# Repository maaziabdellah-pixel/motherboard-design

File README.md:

# Smart Earbuds Charging PCB

A PCB designed to manage charging, battery protection and power delivery for wireless earbuds.
changes:
- Added a new section on the design considerations for the PCB.

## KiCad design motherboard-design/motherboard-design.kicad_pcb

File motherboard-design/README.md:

# Smart Earbuds Charging PCB

A compact 2‑layer PCB that manages charging, protection and power delivery for
the rechargeable battery inside a wireless‑earbuds charging case. It takes 5 V
from a USB Type‑C input, charges a single‑cell 3.7 V Li‑ion battery with a
TP4056, protects the cell with a DW01A + dual‑MOSFET circuit, and shows charge
status on two LEDs.

Designed in **KiCad 10**. Schematic (ERC) and layout (DRC) are both **clean –
0 errors, 0 warnings, 0 unconnected nets.**

---

## 1. Project purpose

| Requirement | How it is met |
|---|---|
| Charge a single‑cell 3.7 V Li‑ion battery | TP4056 linear Li‑ion charger (4.2 V CC/CV) |
| USB‑C input for charging | 16‑pin USB‑C receptacle with CC pull‑downs |
| Overcharge / over‑discharge protection | DW01A protection IC + FS8205A dual N‑MOSFET |
| Charging status indicators | Red LED = charging, Green LED = fully charged |
| Power & ground labels | `+5V`, `+BATT`, `BATT-`, `GND` nets / power symbols |
| Compact, earbuds‑case friendly | 56 × 30 mm, 2‑layer, all SMD |

---

## 2. Components used

| Ref | Part | Footprint | Value / Notes |
|-----|------|-----------|---------------|
| J1 | USB‑C receptacle (USB 2.0, power) | `USB_C_Receptacle_HRO_TYPE-C-31-M-12` | 5 V power input, edge‑mounted |
| U1 | **TP4056** Li‑ion charger | SOIC‑8 | Standalone 4.2 V linear charger |
| U2 | **DW01A** protection IC | SOT‑23‑6 | 1‑cell over‑charge/discharge/current |
| Q1 | **FS8205A** dual N‑MOSFET | SOT‑23‑6 | Back‑to‑back protection switch |
| D1 | LED – **Red** | 0805 | Charging indicator (CHRG) |
| D2 | LED – **Green** | 0805 | Full / standby indicator (STDBY) |
| R1 | 2 kΩ | 0805 | TP4056 `PROG` → ≈ 580 mA charge current |
| R2 | 1 kΩ | 0805 | Red‑LED series resistor |
| R3 | 1 kΩ | 0805 | Green‑LED series resistor |
| R4 | 100 Ω | 0805 | DW01A VDD decoupling resistor |
| R5 | 2 kΩ | 0805 | DW01A `CS` sense resistor |
| R6 | 5.1 kΩ | 0805 | USB‑C `CC1` pull‑down (Rd) |
| R7 | 5.1 kΩ | 0805 | USB‑C `CC2` pull‑down (Rd) |
| C1 | 10 µF | 0805 | VBUS input decoupling |
| C2 | 10 µF | 0805 | Battery / output decoupling |
| C3 | 100 nF | 0805 | DW01A VDD decoupling |
| J2 | Battery connector | JST‑PH 2‑pin SMD | `+BATT` / `BATT-` to the Li‑ion cell |
| J3 | Output connector | JST‑PH 2‑pin SMD | Protected `+BATT` / `GND` to the earbuds |
| H1–H3 | Mounting holes | M2 (2.2 mm) | Mechanical fixing |

All component values follow the TP4056 and DW01A manufacturer reference designs.

### Why these values
* **R1 = 2 kΩ (PROG):** charge current `I = 1200 / R_PROG(kΩ) ≈ 580 mA`, a safe
  ~0.5–1 C rate for the small (typ. 300–800 mAh) cells used in earbuds cases.
  Swap to 1.2 kΩ for 1 A or 5 kΩ for ~240 mA.
* **R6 / R7 = 5.1 kΩ:** the USB‑C spec Rd pull‑downs that tell a USB‑C source
  the board is a sink so it enables 5 V VBUS.
* **R2 / R3 = 1 kΩ:** ≈ 3 mA LED current from the 5 V rail.
* **R4 = 100 Ω + C3 = 100 nF:** DW01A supply RC filter (datasheet typical).

---

## 3. Architecture / signal flow

```
 USB-C 5V ──► TP4056 (charger) ──► +BATT ──┬──► Battery + (J2)
                                            └──► Output + (J3, to earbuds)
 Battery - (B-) ──► FS8205A protection FETs ──► GND (P-) ──► TP4056 / USB return
                         ▲
                       DW01A  (monitors cell voltage & current)
```

* `+5V`  – USB VBUS rail (TP4056 VCC + CE, LEDs, input cap).
* `+BATT`– battery positive = charger output = protected output positive.
* `BATT-`– battery negative (the *protected* node, only the cell + FETs + DW01A GND).
* `GND`  – system / pack‑negative return (USB, TP4056, output −), poured on both layers.

The two protection MOSFETs sit **in the battery's negative return path**, so the
DW01A can interrupt both charge and discharge current.

---

## 4. Charging workflow

1. A USB‑C cable applies **5 V (VBUS)** to the board. `R6`/`R7` (5.1 kΩ on CC1/CC2)
   present the board as a sink, so the source keeps VBUS enabled.
2. **TP4056** charges the cell with a constant‑current / constant‑voltage profile
   up to **4.2 V**. The constant‑current value (~580 mA) is set by `R1` on `PROG`.
   `CE` is tied high (`+5V`) to keep the charger enabled; `TEMP` is tied to `GND`
   (NTC thermistor sensing disabled).
3. While charging, the open‑drain **`CHRG`** output pulls low → **red LED (D1)**
   is on through `R2`.
4. When the cell reaches 4.2 V and the current tapers to ~1/10 of the set value,
   charging stops, **`STDBY`** pulls low → **green LED (D2)** turns on and the red
   LED turns off.
5. `C1` (input) and `C2` (battery side) provide local decoupling per the TP4056
   datasheet.

---

## 5. Battery‑protection workflow

The **DW01A + FS8205A** form a standard 1‑cell protection circuit:

* The DW01A measures the cell voltage across `VDD–VSS` (powered from `+BATT`
  through `R4`, decoupled by `C3`) and the current through the FETs via `CS`
  (referenced to the pack negative `GND` through `R5`).
* The **FS8205A** holds two N‑channel MOSFETs in series (common drain) between the
  cell negative (`BATT-`) and the pack negative (`GND`). One FET gates **charge**
  (`OC`), the other gates **discharge** (`OD`).

| Event | DW01A action | Result |
|---|---|---|
| **Over‑charge** (cell > ~4.3 V) | turns off the charge FET via `OC` | stops further charging |
| **Over‑discharge** (cell < ~2.4 V) | turns off the discharge FET via `OD` | disconnects the load, prevents deep discharge |
| **Over‑current / short** (high V across FETs at `CS`) | turns off both FETs | cuts current, auto‑recovers when fault clears |

Because the FETs are in the common ground return, the protection works for both
the charge path (USB → cell) and the discharge path (cell → earbuds output J3).

---

## 6. Board / layout details

| Spec | Value |
|---|---|
| Size | **56 × 30 mm** (compact, fits a charging‑case base) |
| Layers | **2** (F.Cu + B.Cu) |
| Copper | GND **pour on both layers**, stitched with vias |
| Power traces | **0.5 mm** (`+5V`, `+BATT`, `BATT-`, `GND` → *Power* net class) |
| Signal traces | **0.3 mm** |
| Clearance | 0.2 mm | 
| Vias | 0.6 mm / 0.3 mm drill |
| USB‑C | on the **left board edge**, opening facing off‑board |
| Connectors | battery (J2) and output (J3) on the right edge |
| Mounting holes | 3 × M2 |

Good‑practice points applied: USB‑C on the board edge, wide low‑impedance power
traces, a continuous ground pour separating/return‑pathing the signals, signal
vs. power routing kept apart, and silkscreen labels (`USB‑C`, `CHG`, `FULL`,
`BAT`, `OUT`, board title).

---

## 7. Files

```
motherboard-design.kicad_pro   KiCad 10 project (Default + Power net classes)
motherboard-design.kicad_sch   Schematic
motherboard-design.kicad_pcb   PCB layout (routed, zones filled)
EarbudsCharger.kicad_sym       Project symbol library (TP4056, DW01A, FS8205A)
sym-lib-table                  Registers the project symbol library
README.md                      This document
docs/schematic.pdf             Schematic export
docs/pcb_top.png               3D render – top
docs/pcb_bottom.png            3D render – bottom
docs/erc_report.rpt            ERC result (0 violations)
docs/drc_report.rpt            DRC result (0 violations)
tools/gen_schematic.py         Reproducible schematic generator
tools/gen_pcb.py               Reproducible PCB generator + maze router
```

The three ICs (TP4056, DW01A, FS8205A) are not in the stock KiCad libraries, so
they are provided as a project symbol library (`EarbudsCharger.kicad_sym`) and are
also embedded in the schematic.

---

## 8. Verification

```
ERC : 0 errors, 0 warnings           (kicad-cli sch erc)
DRC : 0 violations, 0 unconnected     (kicad-cli pcb drc)
```

To re‑check:

```sh
kicad-cli sch erc  motherboard-design.kicad_sch
kicad-cli pcb drc  motherboard-design.kicad_pcb
```

---

## 9. Opening the project

Open `motherboard-design.kicad_pro` in **KiCad 10**.

> The board is fully routed with both ground planes filled. If you edit the
> layout, run **Edit → Fill All Zones (B)** and re‑run DRC.

### ⚠️ Note on regeneration
The PCB is built programmatically by `tools/gen_pcb.py` using the KiCad `pcbnew`
Python API; the schematic by `tools/gen_schematic.py`. Re‑running them recreates
the `.kicad_sch` / `.kicad_pcb` from scratch, so close the project in the KiCad
GUI before regenerating (an open GUI session can overwrite the generated files
when it saves).

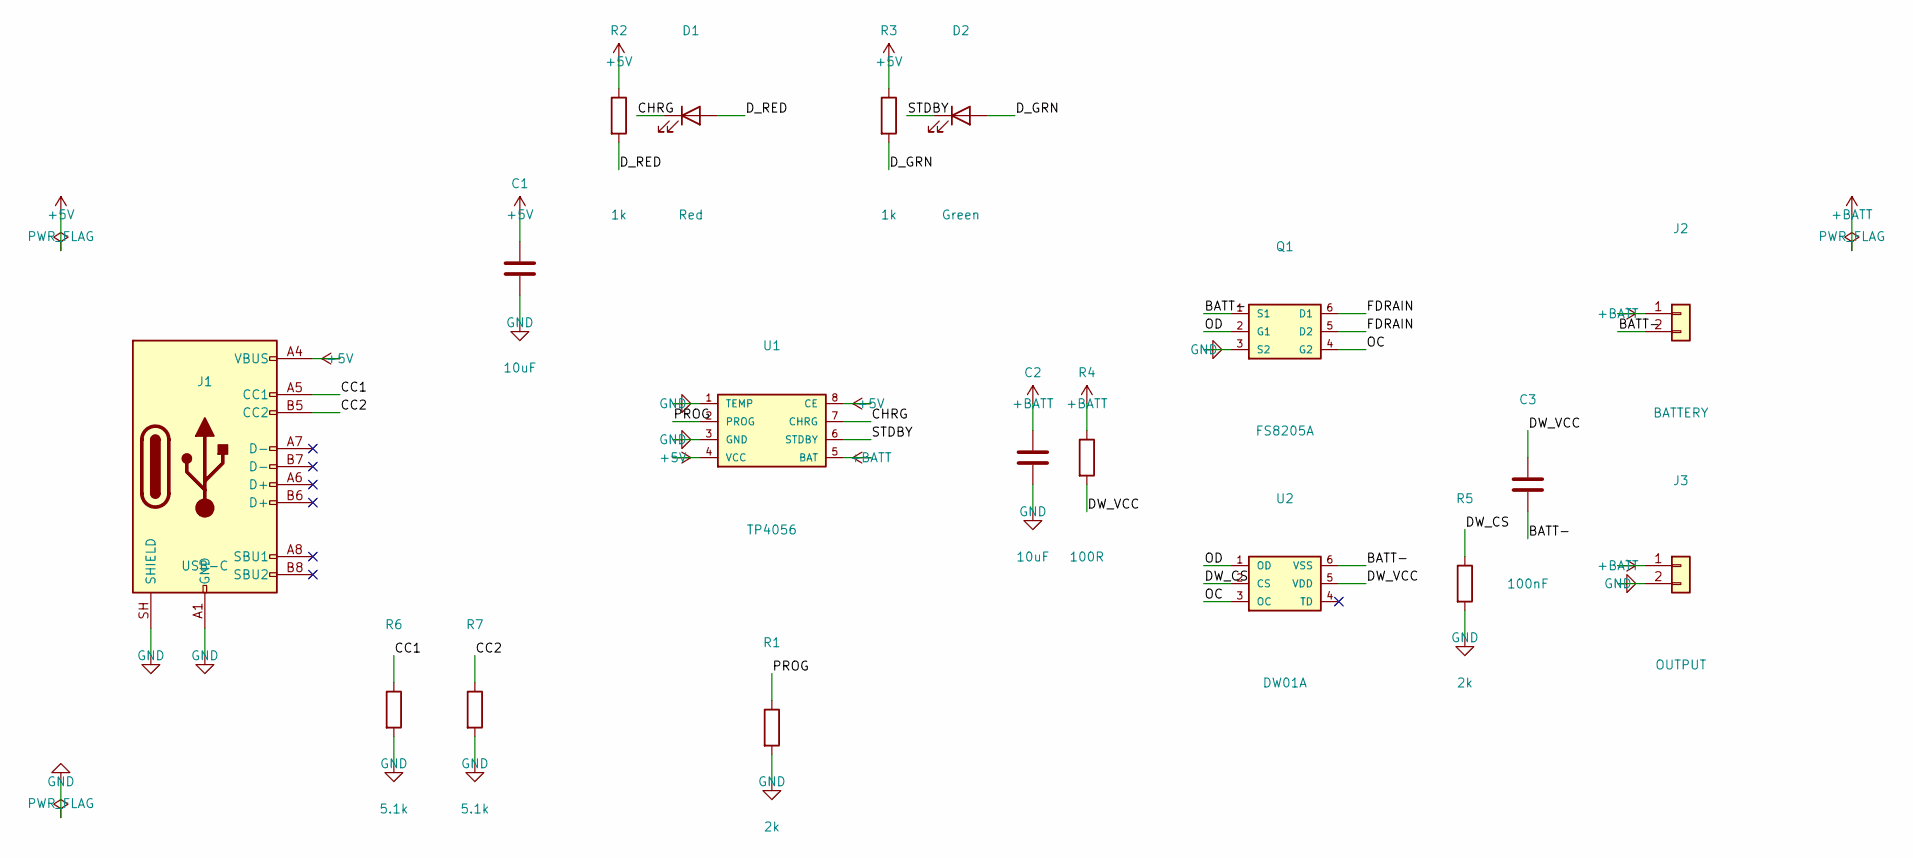
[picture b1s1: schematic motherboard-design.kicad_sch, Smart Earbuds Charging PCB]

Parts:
C1, C2: 10uF; C_0805_2012Metric
C3: 100nF; C_0805_2012Metric
D1: Red; LED_0805_2012Metric
D2: Green; LED_0805_2012Metric
J1: USB-C; USB_C_Receptacle_HRO_TYPE-C-31-M-12
J2: BATTERY; JST_PH_B2B-PH-SM4-TB_1x02-1MP_P2.00mm_Vertical
J3: OUTPUT; JST_PH_B2B-PH-SM4-TB_1x02-1MP_P2.00mm_Vertical
Q1: FS8205A; SOT-23-6
R1, R5: 2k; R_0805_2012Metric
R2, R3: 1k; R_0805_2012Metric
R4: 100R; R_0805_2012Metric
R6, R7: 5.1k; R_0805_2012Metric
U1: TP4056; SOIC-8_3.9x4.9mm_P1.27mm
U2: DW01A; SOT-23-6

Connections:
+5V: C1.1, J1.A4 (VBUS), J1.A9 (VBUS), J1.B4 (VBUS), J1.B9 (VBUS), R2.1, R3.1, U1.4 (VCC), U1.8 (CE)
+BATT: C2.1, J2.1, J3.1, R4.1, U1.5 (BAT)
BATT-: C3.2, J2.2, Q1.1 (S1), U2.6 (VSS)
CC1: J1.A5 (CC1), R6.1
CC2: J1.B5 (CC2), R7.1
CHRG: D1.1 (K), U1.7 (CHRG)
DW_CS: R5.1, U2.2 (CS)
DW_VCC: C3.1, R4.2, U2.5 (VDD)
D_GRN: D2.2 (A), R3.2
D_RED: D1.2 (A), R2.2
FDRAIN: Q1.5 (D2), Q1.6 (D1)
GND: C1.2, C2.2, J1.A1 (GND), J1.A12 (GND), J1.B1 (GND), J1.B12 (GND), J1.SH (SHIELD), J3.2, Q1.3 (S2), R1.2, R5.2, R6.2, R7.2, U1.1 (TEMP), U1.3 (GND)
OC: Q1.4 (G2), U2.3 (OC)
OD: Q1.2 (G1), U2.1 (OD)
PROG: R1.1, U1.2 (PROG)
STDBY: D2.1 (K), U1.6 (STDBY)

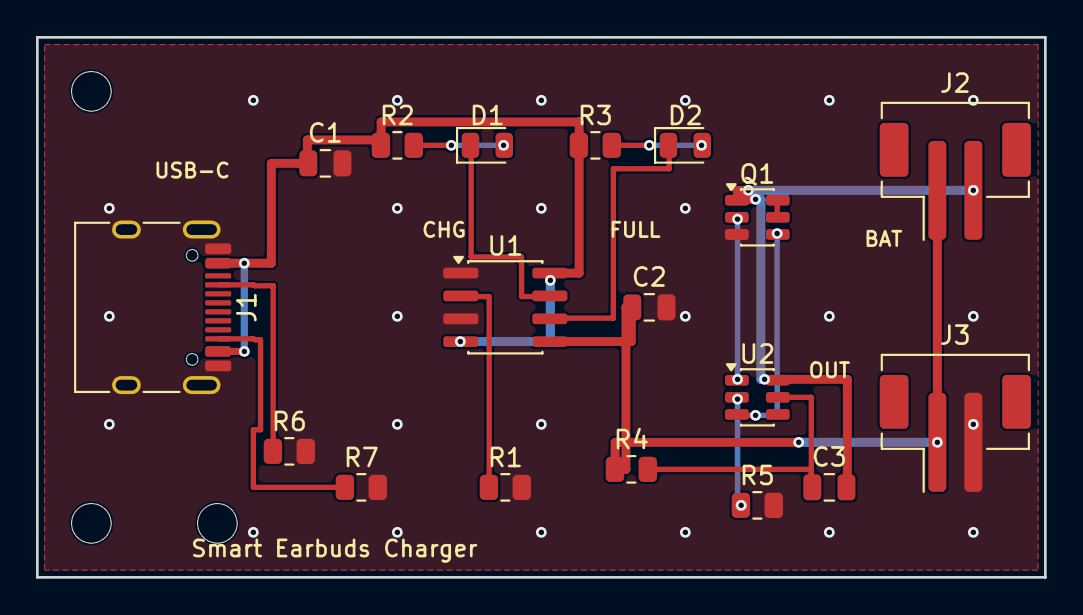
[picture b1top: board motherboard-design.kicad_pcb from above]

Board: 2 copper layers, 56.0 x 30.0 mm, 21 parts (0 on the bottom side), 16 nets.

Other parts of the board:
H1, H2, H3: MountingHole_2.2mm_M2

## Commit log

2026-06-05 add plan
2026-06-06 Add project files with gitignore
2026-06-06 Remove tools directory
